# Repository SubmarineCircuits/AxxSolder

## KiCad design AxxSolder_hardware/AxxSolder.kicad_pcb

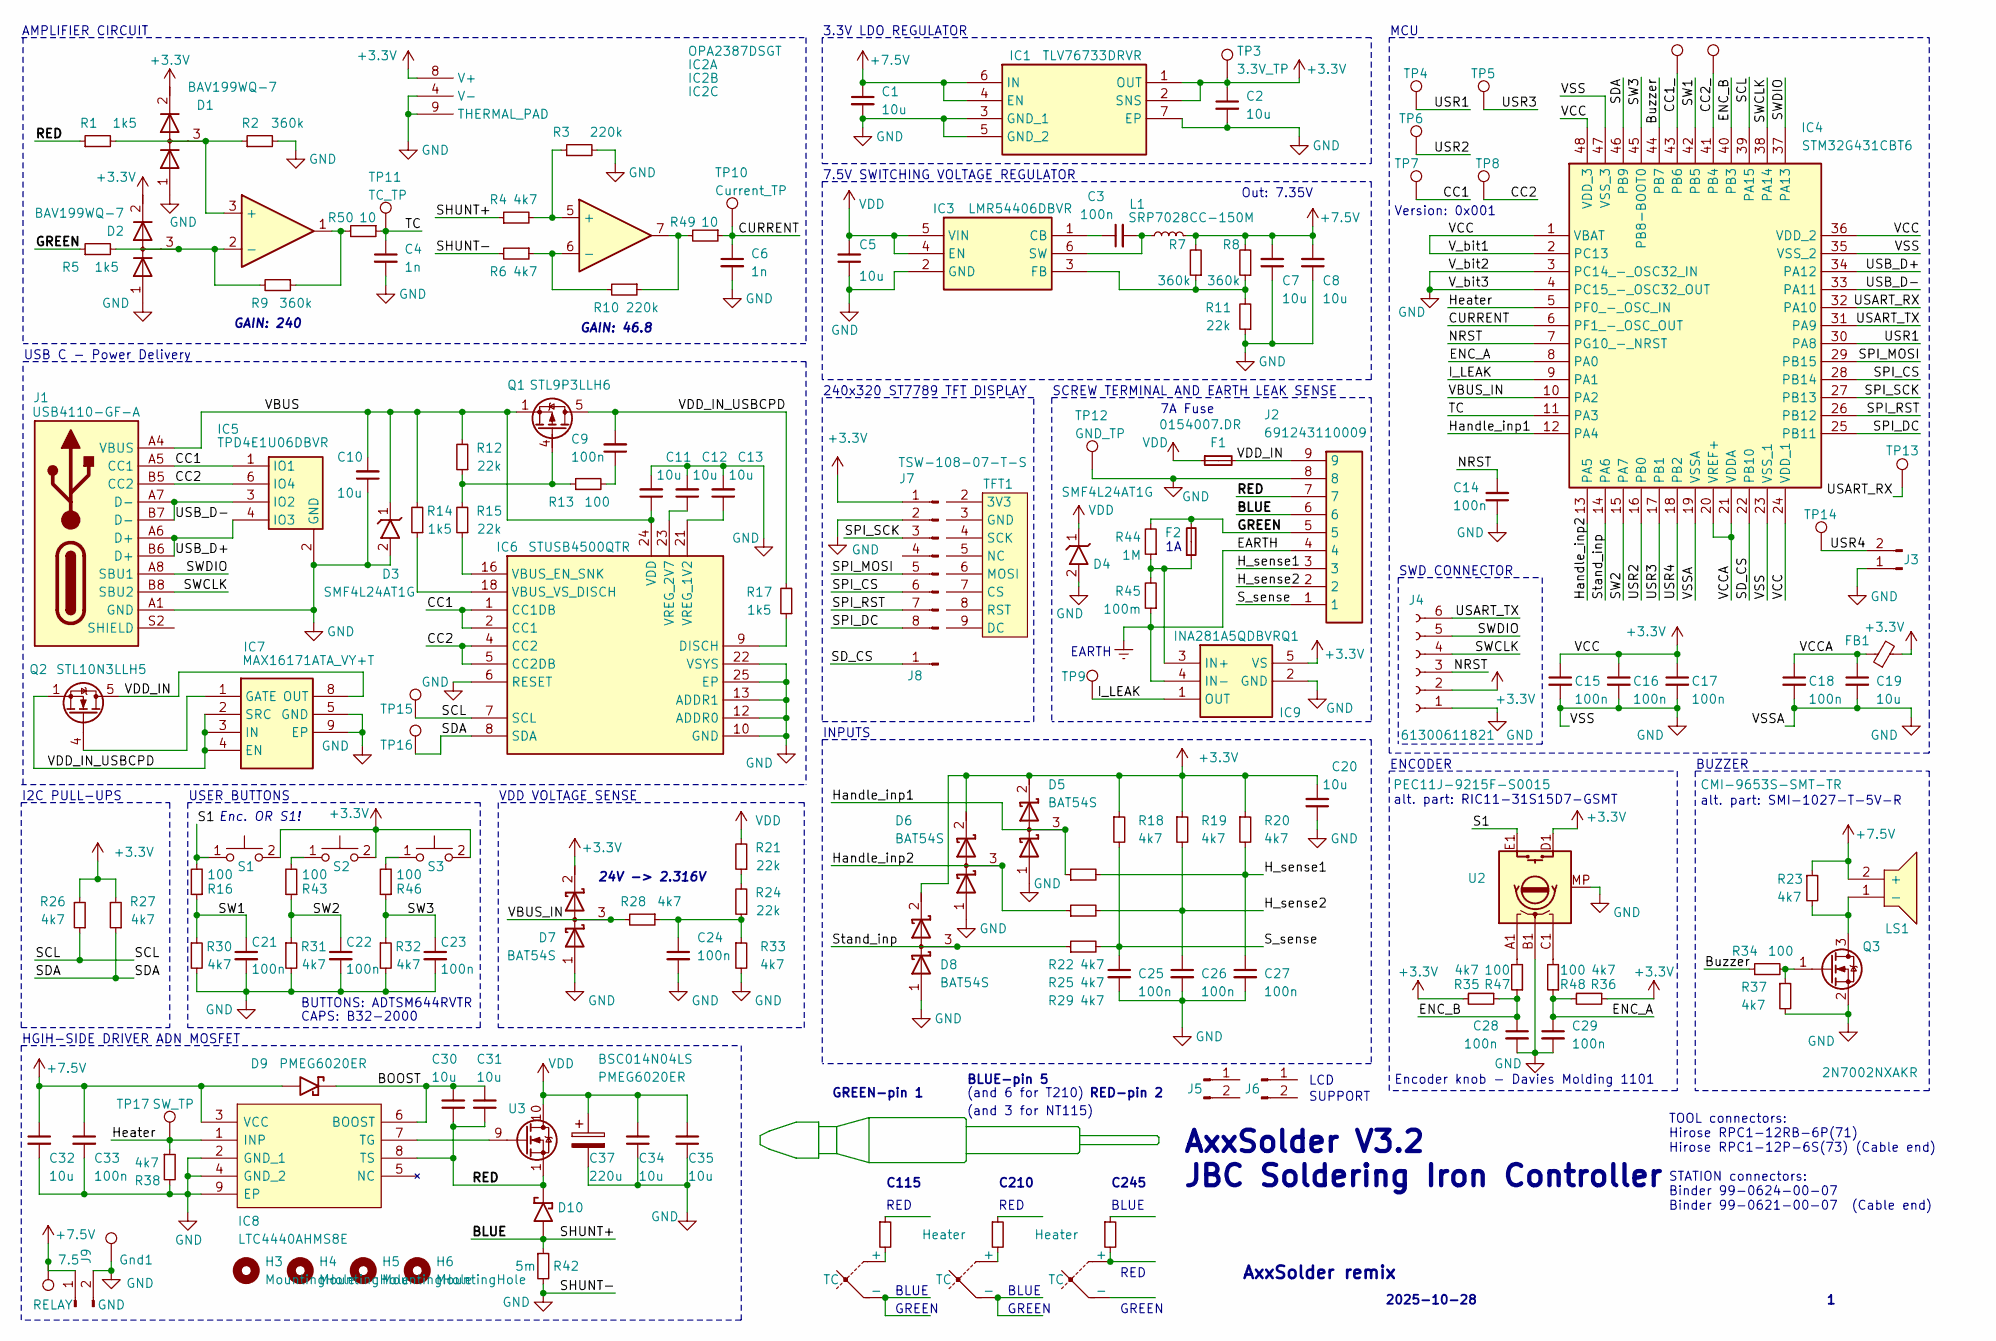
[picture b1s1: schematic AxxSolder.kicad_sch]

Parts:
7.5: RELAY; TestPoint_Keystone_5019_Miniature
C1, C2, C5, C7, C8, C10, C11, C12, C13, C19, C20, C30, C31, C32, C34, C35: 10u; C_0603_1608Metric; Manufacturer_Part_Number GRM188R6YA106MA73J; Mouser Part Number 81-GRM188R6YA106MA3J
C3, C9, C14, C15, C16, C17, C18, C21, C22, C23, C24, C25, C26, C27, C28, C29, C33: 100n; C_0603_1608Metric; Manufacturer_Part_Number C0603C104J5RACTU; Mouser Part Number 80-C0603C104J5R
C4, C6: 1n; C_0603_1608Metric; Manufacturer_Part_Number C0603C102K3GAC; Mouser Part Number 80-C0603C102K3G
C37: 220u; CAPAE830X1050N; Mouser Part Number 80-EEV227M035A9MAA
D1, D2: BAV199WQ-7; SOT65P210X110-3N; Mouser Part Number 621-BAV199WQ-7
D3, D4: SMF4L24AT1G; SODFL3619X98N; Mouser Part Number 576-SMF4L24AT1G
D5, D6, D7, D8: BAT54S; SOT95P230X110-3N; Manufacturer_Part_Number BAT54S,215; Mouser Part Number 771-BAT54S-T/R
D9, D10: PMEG6020ER; PMEG6020ER115; Mouser Part Number 771-PMEG6020ER-115
F1: 0154007.DR; 0154100DR; Mouser Part Number 576-0154007.DR
F2: SF-2410FP100W-2; SF2410FP100W2; Mouser Part Number 652-SF-2410FP100W-2
FB1: BLM18HE601SN1D; R_0603_1608Metric; Mouser Part Number 81-BLM18HE601SN1D
Gnd1: GND; TestPoint_Keystone_5019_Miniature
H3, H4, H5, H6: MountingHole; MountingHole_3.2mm_M3
IC1: TLV76733DRVR; SON65P200X200X80-7N; Mouser Part Number 595-TLV76733DRVR
IC2: OPA2387DSGT; SON50P200X200X80-9N; Mouser Part Number 595-OPA2387DSGT
IC3: LMR54406DBVR; SOT95P280X145-6N; Mouser Part Number 595-LMR54406DBVR
IC4: STM32G431CBT6; QFP50P900X900X160-48N; Mouser Part Number 511-STM32G431CBT6
IC5: TPD4E1U06DBVR; SOT95P280X145-6N; Mouser Part Number 595-TPD4E1U06DBVR
IC6: STUSB4500QTR; QFN50P400X400X100-25N-D; Mouser Part Number 511-STUSB4500QTR
IC7: MAX16171ATA_VY+T; SON50P300X200X80-9N; Mouser Part Number 700-MAX16171ATA/VY+T
IC8: LTC4440AHMS8E; SOP65P490X110-9N; Mouser Part Number 584-C4440AHMS8E-5PBF
IC9: INA281A5QDBVRQ1; SOT95P280X145-5N; Mouser Part Number 595-INA281A5QDBVRQ1
J1: USB4110-GF-A; USB4110GFA; Mouser Part Number 640-USB4110-GF-A
J2: 691243110009; Mouser Part Number 710-691243110009
J3: TSW-102-07-T-S; PinHeader_1x02_P2.54mm_Vertical; Mouser Part Number 200-TSW10207TS
J4: 61300611821; RHDR6W97P0X254_1X6_1574X250X865P; Mouser Part Number 710-61300611821
J5, J6, J9: TSW-102-07-T-S; TSW-102-XX-YY-S; Mouser Part Number 200-TSW10207TS
J7: TSW-108-07-T-S; TSW-108-XX-YY-S; Mouser Part Number 200-TSW10807TS
J8: Conn_01x01_Pin; TSW-101-XX-YY-S
L1: SRP7028CC-150M; INDPM7366X300N; Mouser Part Number 652-SRP7028CC-150M
LS1: CMI-9653S-SMT-TR; CMI9653SSMTTR; Mouser Part Number 490-CMI-9653S-SMT-TR
Q1: STL9P3LLH6; Mouser Part Number 511-STL9P3LLH6
Q2: STL10N3LLH5; Mouser Part Number 511-STL10N3LLH5
Q3: 2N7002NXAKR; SOT95P230X110-3N; Manufacturer_Part_Number 2N7002NXAKR; Mouser Part Number 771-2N7002NXAKR
R1, R5, R14, R17: 1k5; R_0603_1608Metric; Manufacturer_Part_Number ERJ-H3ED1501V; Mouser Part Number 667-ERJ-H3ED1501V
R2, R7, R8, R9: 360k; R_0603_1608Metric; Manufacturer_Part_Number ERJ-3RED3603V; Mouser Part Number 667-ERJ-3RED3603V
R3, R10: 220k; R_0603_1608Metric; Manufacturer_Part_Number ERJ-3RED2203V; Mouser Part Number 667-ERJ-3RED2203V
R4, R6, R18, R19, R20, R22, R23, R25, R26, R27, R28, R29, R30, R31, R32, R33, R35, R36, R37, R38: 4k7; R_0603_1608Metric; Manufacturer_Part_Number ERJ-3RBD4701V; Mouser Part Number 667-ERJ-3RBD4701V
R11, R12, R15, R21, R24: 22k; R_0603_1608Metric; Manufacturer_Part_Number ERJ-UP3J223V; Mouser Part Number 667-ERJ-UP3J223V
R13, R16, R34, R43, R46, R47, R48: 100; R_0603_1608Metric; Manufacturer_Part_Number ERJ-P03F1000V; Mouser Part Number 667-ERJ-P03F1000V
R39, R40: Heater
R41: Heater 2 OHM
R42: 5m; RESC6432X89N; Mouser Part Number 71-WSLP25125L000FEA
R44: 1M; R_0805_2012Metric; Manufacturer_Part_Number ERJ-6GEYJ105V; Mouser Part Number 667-ERJ-6GEYJ105V
R45: 100m; R_0805_2012Metric; Manufacturer_Part_Number ERJ-6DSFR10V; Mouser Part Number 667-ERJ-6DSFR10V
R49, R50: 10; R_0603_1608Metric; Manufacturer_Part_Number ERJ-3RED10R0V; Mouser Part Number 667-ERJ-3RED10R0V
S1, S2, S3: ADTSM644RVTR; Mouser Part Number 642-ADTSM644RVTR
TC1, TC2, TC3: TC
TFT1: Adafruit_240x320_TFT; Manufacturer_Part_Number 4311; Mouser Part Number 485-4311
TP1, TP2, TP4, TP5, TP6, TP7, TP8, TP14, TP15, TP16: DIAG_TP; TestPoint_Pad_D1.0mm
TP3: 3.3V_TP; TestPoint_Pad_D1.0mm
TP9, TP10: Current_TP; TestPoint_Pad_D1.0mm
TP11: TC_TP; TestPoint_Pad_D1.0mm
TP12: GND_TP; TestPoint_Pad_D1.0mm
TP13: DIAG_TP; TSW-101-XX-YY-S
TP17: SW_TP; TestPoint_Pad_D1.0mm
U2: PEC11J-9215F-S0015; PEC11J9215FS0015; Mouser Part Number 652-PEC11J9215FS0015
U3: BSC014N04LS; Manufacturer_Part_Number BSC014N04LSATMA1; Mouser Part Number 726-BSC014N04LSATMA1

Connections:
+3.3V: C2.1, C15.1, C16.1, C17.1, C20.2, D1.2, D2.2, D5.2 (K), D6.2 (K), D7.2 (K), D8.2 (K), FB1.2, IC1.1 (OUT), IC1.2 (SNS), IC2.8 (V+), IC4.1 (VBAT), IC4.2 (PC13), IC4.24 (VDD_1), IC4.36 (VDD_2), IC4.48 (VDD_3), IC9.5 (VS), J4.2, J7.1, R18.1, R19.1, R20.1, R26.2, R27.2, R35.2, R36.1, S1.2, S2.2, S3.2, TP3.1, U2.D1
+7.5V: 7.5.1, C1.1, C7.2, C8.2, C32.1, C33.1, D9.2, IC1.4 (EN), IC1.6 (IN), IC8.3 (VCC), J9.1, L1.2, LS1.2 (+), R7.2, R8.2, R23.1
/BLUE: D10.2, J2.6, R4.1, R42.1
/BOOST: C30.2, C31.2, D9.1, IC8.6 (BOOST)
/Buzzer: IC4.44 (PB7), R34.1
/CC1: IC5.1 (IO1), IC6.1 (CC1DB), IC6.2 (CC1), J1.A5 (CC1), TP7.1
/CC1_: IC4.43 (PB6), TP1.1
/CC2: IC5.6 (IO4), IC6.4 (CC2), IC6.5 (CC2DB), J1.B5 (CC2), TP8.1
/CC2_: IC4.41 (PB4), TP2.1
/CURRENT: C6.1, IC4.6 (PF1_-_OSC_OUT), R49.1, TP10.1
/ENC_A: C29.1, IC4.8 (PA0), R36.2, R48.1
/ENC_B: C28.1, IC4.40 (PB3), R35.1, R47.1
/GREEN: F2.2, J2.5, R5.1, R44.2
/H_sense1: C27.1, J2.3, R20.2, R22.2
/H_sense2: C26.1, J2.2, R19.2, R25.2
/Handle_inp1: D5.3 (common), IC4.12 (PA4), R22.1
/Handle_inp2: D6.3 (common), IC4.13 (PA5), R25.1
/Heater: IC4.5 (PF0_-_OSC_IN), IC8.1 (INP), R38.1, TP17.1
/I_LEAK: IC4.9 (PA1), IC9.1 (OUT), TP9.1
/NRST: C14.2, IC4.7 (PG10_-_NRST), J4.3
/RED: C30.1, C31.1, D10.1, IC8.8 (TS), J2.7, R1.1, U3.1 (S)
/S1: R16.2, S1.1, U2.E1
/SCL: IC4.39 (PA15), IC6.7 (SCL), R26.1, TP15.1
/SDA: IC4.46 (PB9), IC6.8 (SDA), R27.1, TP16.1
/SD_CS: IC4.22 (PB10), J8.1
/SPI_CS: IC4.28 (PB14), J7.6
/SPI_DC: IC4.25 (PB11), J7.8
/SPI_MOSI: IC4.29 (PB15), J7.5
/SPI_RST: IC4.26 (PB12), J7.7
/SPI_SCK: IC4.27 (PB13), J7.3
/SW1: C21.1, IC4.42 (PB5), R16.1, R30.1
/SW2: C22.1, IC4.15 (PA7), R31.1, R43.1
/SW3: C23.1, IC4.45 (PB8-BOOT0), R32.1, R46.1
/SWCLK: IC4.38 (PA14), J1.B8 (SBU2), J4.4
/SWDIO: IC4.37 (PA13), J1.A8 (SBU1), J4.5
/S_sense: C25.1, J2.1, R18.2, R29.2
/Stand_inp: D8.3 (common), IC4.14 (PA6), R29.1
/TC: C4.1, IC4.11 (PA3), R50.1, TP11.1
/USART_RX: IC4.32 (PA10), TP13.1
/USART_TX: IC4.31 (PA9), J4.6
/USB_D+: IC4.34 (PA12), IC5.4 (IO3), J1.A6 (D+), J1.B6 (D+)
/USB_D-: IC4.33 (PA11), IC5.3 (IO2), J1.A7 (D-), J1.B7 (D-)
/USR1: IC4.30 (PA8), TP4.1
/USR2: IC4.16 (PB0), TP6.1
/USR3: IC4.17 (PB1), TP5.1
/USR4: IC4.18 (PB2), J3.2, TP14.1
/VBUS: C10.2, C11.1, D3.1 (K), IC6.24 (VDD), J1.A4 (VBUS), J1.A9 (VBUS), J1.B4 (VBUS), J1.B9 (VBUS), Q1.1 (S), R12.2, R14.2
/VBUS_IN: D7.3 (common), IC4.10 (PA2), R28.2
/VCCA: C18.1, C19.1, FB1.1, IC4.20 (VREF+), IC4.21 (VDDA)
/VDD_IN: F1.2, IC7.8 (OUT), J2.9, Q2.5 (D)
/VDD_IN_USBCPD: C9.2, IC7.2 (SRC), IC7.3 (IN), IC7.4 (EN), Q1.5 (D), Q2.1 (S), R17.2
Earth: IC9.4 (IN-), J2.4, R45.1
GND: C1.2, C2.2, C4.2, C5.1, C6.2, C7.1, C8.1, C10.1, C11.2, C12.2, C13.2, C14.1, C15.2, C16.2, C17.2, C18.2, C19.2, C20.1, C21.2, C22.2, C23.2, C24.2, C25.2, C26.2, C27.2, C28.2, C29.2, C32.2, C33.2, C34.1, C35.1, C37.2, D1.1, D2.1, D3.2 (A), D4.2 (A), D5.1 (A), D6.1 (A), D7.1 (A), D8.1 (A), Gnd1.1, IC1.3 (GND_1), IC1.5 (GND_2), IC1.7 (EP), IC2.4 (V-), IC2.9 (THERMAL_PAD), IC3.2 (GND), IC4.3 (PC14_-_OSC32_IN), IC4.4 (PC15_-_OSC32_OUT), IC4.19 (VSSA), IC4.23 (VSS_1), IC4.35 (VSS_2), IC4.47 (VSS_3), IC5.2 (GND), IC6.6 (RESET), IC6.10 (GND), IC6.12 (ADDR0), IC6.13 (ADDR1), IC6.22 (VSYS), IC6.25 (EP), IC7.5 (GND), IC7.9 (EP), IC8.2 (GND_1), IC8.4 (GND_2), IC8.9 (EP), IC9.2 (GND), J1.A1 (GND), J1.A12 (GND), J1.B1 (GND), J1.B12 (GND), J2.8, J3.1, J4.1, J7.2, J9.2, Q3.2 (S), R2.2, R3.2, R6.2, R11.1, R30.2, R31.2, R32.2, R33.2, R37.2, R38.2, R42.2, TP12.1, U2.B1, U2.MP
unnamed: C9.1, R13.2
unnamed: C24.1, R24.1, R28.1, R33.1
unnamed: IC2.1, R9.1, R50.2
unnamed: IC2.7, R10.1, R49.2
unnamed: D1.3, IC2.3 (+), R1.2, R2.1
unnamed: D2.3, IC2.2 (-), R5.2, R9.2
unnamed: IC2.5 (+), R3.1, R4.2
unnamed: IC2.6 (-), R6.1, R10.2
unnamed: C3.1, IC3.1 (CB)
unnamed: IC3.3 (FB), R7.1, R8.1, R11.2
unnamed: C3.2, IC3.6 (SW), L1.1
unnamed: IC6.9 (DISCH), R17.1
unnamed: IC6.16 (VBUS_EN_SNK), R15.1
unnamed: IC6.18 (VBUS_VS_DISCH), R14.1
unnamed: C13.1, IC6.21 (VREG_1V2)
unnamed: C12.1, IC6.23 (VREG_2V7)
unnamed: IC7.1 (GATE), Q2.4 (G)
unnamed: IC8.7 (TG), U3.9 (G)
unnamed: F2.1, IC9.3 (IN+), R44.1, R45.2
unnamed: LS1.1 (-), Q3.3 (D), R23.2
unnamed: Q1.4 (G), R12.1, R13.1, R15.2
unnamed: Q3.1 (G), R34.2, R37.1
unnamed: R21.1, R24.2
unnamed: R39.2, TC1.1 (+)
unnamed: R40.2, TC2.1 (+)
unnamed: R41.2, TC3.1 (+)
unnamed: R43.2, S2.1
unnamed: R46.2, S3.1
unnamed: R47.2, U2.A1
unnamed: R48.2, U2.C1
VDD: C5.2, C34.2, C35.2, C37.1, D4.1 (K), F1.1, IC3.4 (EN), IC3.5 (VIN), R21.2, U3.10 (D)

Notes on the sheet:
Version: 0x001
USER BUTTONS
C115
7A Fuse
Encoder knob - Davies Molding 1101
USB C - Power Delivery
BUTTONS: ADTSM644RVTR
Enc. OR S1!
MCU
CAPS: B32-2000
GREEN
(and 3 for NT115)
GREEN-pin 1
RED
LCD
alt. part: SMI-1027-T-5V-R
(and 6 for T210)
SCREW TERMINAL AND EARTH LEAK SENSE
AMPLIFIER CIRCUIT
24V -> 2.316V
VDD VOLTAGE SENSE
C245
ENCODER
SWD CONNECTOR
BLUE
BLUE-pin 5
2025-10-28
BUZZER
7.5V SWITCHING VOLTAGE REGULATOR
AxxSolder V3.2 JBC Soldering Iron Controller
TOOL connectors: Hirose RPC1-12RB-6P(71) Hirose RPC1-12P-6S(73) (Cable end) STATION connectors: Binder 99-0624-00-07 Binder 99-0621-00-07 (Cable end)
C210
INPUTS
EARTH
HGIH-SIDE DRIVER ADN MOSFET
AxxSolder remix
RED-pin 2
RED
Out: 7.35V
I2C PULL-UPS

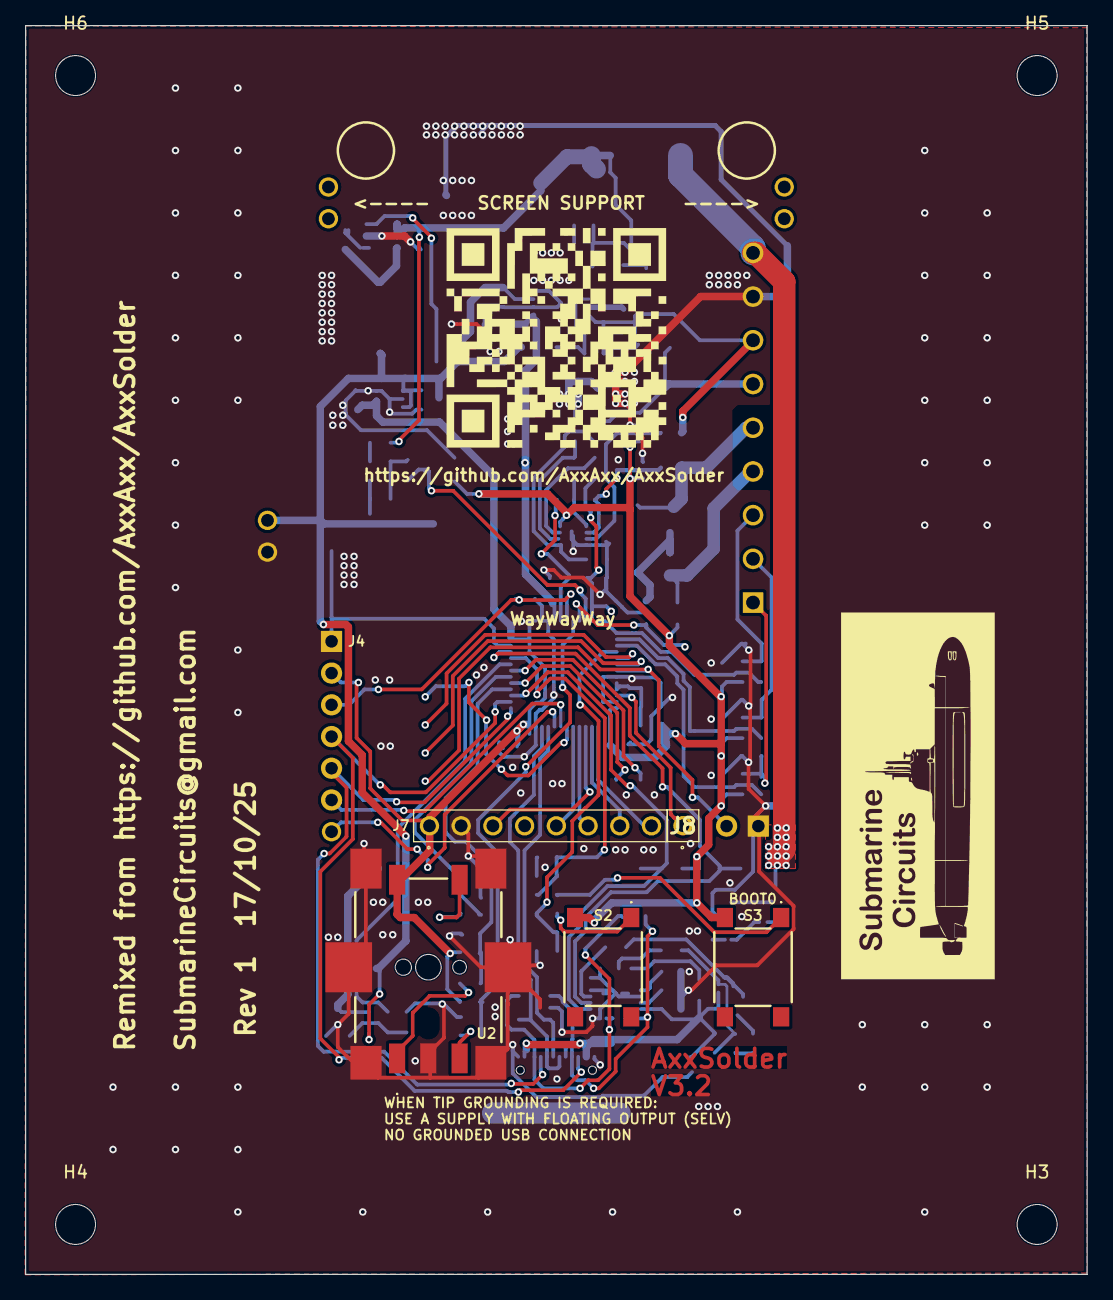
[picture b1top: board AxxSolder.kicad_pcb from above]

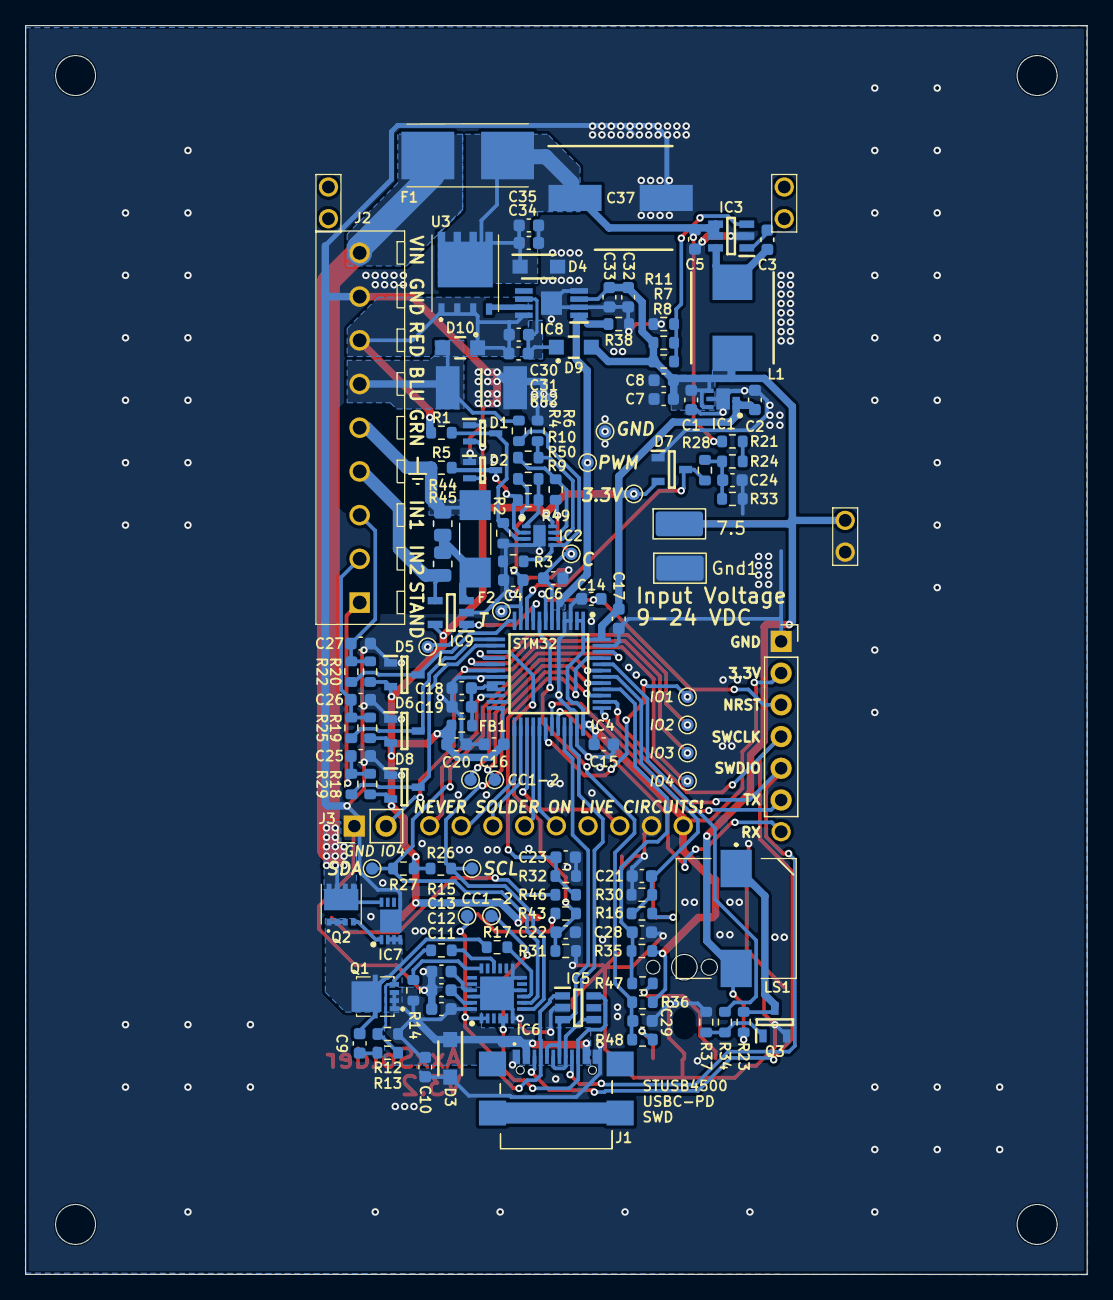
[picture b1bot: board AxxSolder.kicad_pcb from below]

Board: 2 copper layers, 85.0 x 100.0 mm, 146 parts (133 on the bottom side), 81 nets.

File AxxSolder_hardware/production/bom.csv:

Designator,Footprint,Quantity,Value,LCSC Part #
7.5V,TestPoint_Keystone_5019_Miniature,1,RELAY,
"C1, C10, C11, C12, C13, C19, C2, C20, C30, C31, C32, C34, C35, C5, C7, C8",0603,16,10u,
"C14, C15, C16, C17, C18, C21, C22, C23, C24, C25, C26, C27, C28, C29, C3, C33, C9",0603,17,100n,
C37,CAPAE830X1050N,1,220u,
"C4, C6",0603,2,1n,
"D1, D2",SOT65P210X110-3N,2,BAV199WQ-7,
"D10, D9",PMEG6020ER115,2,PMEG6020ER,
"D3, D4",SODFL3619X98N,2,SMF4L24AT1G,
"D5, D6, D7, D8",SOT95P230X110-3N,4,BAT54S,
F1,0154100DR,1,0154007.DR,
F2,SF2410FP100W2,1,SF-2410FP100W-2,
FB1,0603,1,BLM18HE601SN1D,
G,TestPoint_Keystone_5019_Miniature,1,GND,
IC1,SON65P200X200X80-7N,1,TLV76733DRVR,
IC2,SON50P200X200X80-9N,1,OPA2387DSGT,
IC3,SOT95P280X145-6N,1,LMR54406DBVR,
IC4,QFP50P900X900X160-48N,1,STM32G431CBT6,
IC5,SOT95P280X145-6N,1,TPD4E1U06DBVR,
IC6,QFN50P400X400X100-25N-D,1,STUSB4500QTR,
IC7,SON50P300X200X80-9N,1,MAX16171ATA_VY+T,
IC8,SOP65P490X110-9N,1,LTC4440AHMS8E,
IC9,SOT95P280X145-5N,1,INA281A5QDBVRQ1,
J1,USB4110GFA,1,USB4110-GF-A,
J2,691243110009,1,691243110009,
J4,RHDR6W97P0X254_1X6_1574X250X865P,1,61300611821,
"J5, J6",TSW-102-XX-YY-S,2,TSW-102-07-T-S,
J7,TSW-108-XX-YY-S,1,TSW-108-07-T-S,
L1,INDPM7366X300N,1,SRP7028CC-150M,
LS1,CMI9653SSMTTR,1,CMI-9653S-SMT-TR,
Q1,STL9P3LLH6,1,STL9P3LLH6,
Q2,STL10N3LLH5,1,STL10N3LLH5,
Q3,SOT95P230X110-3N,1,2N7002NXAKR,
"R1, R14, R17, R5",0603,4,1k5,
"R10, R3",0603,2,220k,
"R11, R12, R15, R21, R24",0603,5,22k,
"R13, R16, R34, R43, R46, R47, R48",0603,7,100,
"R18, R19, R20, R22, R23, R25, R26, R27, R28, R29, R30, R31, R32, R33, R35, R36, R37, R38, R4, R6",0603,20,4k7,
"R2, R7, R8, R9",0603,4,360k,
R42,RESC6432X89N,1,5m,
R44,0805,1,1M,
R45,0805,1,100m,
"R49, R50",0603,2,10,
"S1, S2, S3",ADTSM644RVTR,3,ADTSM644RVTR,
TFT1,Adafruit_240x320_TFT,1,~,
U2,PEC11J9215FS0015,1,PEC11J-9215F-S0015,
U3,BSC014N04LS,1,BSC014N04LS,

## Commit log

2025-10-07 added pwr connections for relay add on board
2025-10-07 new production files
2025-10-08 enlarged PCB
2025-10-17 enlarged board
2025-10-17 updated layout
2025-10-28 deleted fuducials
2025-10-28 added stitching vias
